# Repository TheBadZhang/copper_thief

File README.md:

# Copper Thief / KiCad 盗铜生成器

在 `Edge.Cuts` 板框内，按规则阵列自动生成**圆形**或**圆角正方形**盗铜（copper thieving），并自动避让已有铜箔、板边、板框开槽、禁布区和钻孔。

> 上图由本插件在 `demo/copper_thief_demo.kicad_pcb` 上实际生成，并经过 KiCad 10.0.6 DRC 验证（0 violations / 0 unconnected）。

---

## 1. 功能

- 图案：圆形，或四边相等的圆角正方形。
- 可调直径 / 边长、圆角半径、阵列净间距。
- 可调铜箔间距、板边间距；实际值会与板级 DRC 规则取较大者。
- 在板框内自动居中，也可设置 X/Y 偏移。
- 支持任意铜层：F.Cu、B.Cu、内层。
- 自动避让：
  - 走线、圆弧走线、过孔、焊盘（含 PTH/NPTH/SMD/自定义焊盘）
  - 已填充的铜区（Zone），包括铜区中的孔洞
  - 铜层上的图形、文字、封装图形
  - 板框开槽、圆孔、异形孔
  - 焊盘/过孔钻孔（含槽孔）
  - 禁布区 / Rule Area（保守处理：整个区域都避开）
- 与已有铜箔相交、间距不足或落在板外时**自动跳过**，并在预览中统计跳过原因。
- 生成结果统一放在一个 `CopperThief` 组中，可用“删除现有盗铜”一键清理。
- 支持“同时避开相同网络铜箔”选项。
- 支持**项目配置文件** `<板名>.copper_thief.json`，可保存任意多个命名配置，下次打开项目直接选择复用。
- 再次生成时可选择“替换整个组”或“追加到同一个组”，不会产生多个难以管理的组。

---

## 2. 安装

### 方式 A：运行安装脚本（推荐）

在 PowerShell 中：

```powershell
cd C:\Users\lab\Desktop\copper_thief
powershell -ExecutionPolicy Bypass -File .\install.ps1
```

默认安装到：

```text
%APPDATA%\kicad\10.0\scripting\plugins\copper_thief
```

如果使用 KiCad 9，可指定版本：

```powershell
powershell -ExecutionPolicy Bypass -File .\install.ps1 -Version 9.0
```

### 方式 B：手动复制

把整个 `copper_thief` 文件夹复制到：

```text
C:\Users\<用户名>\AppData\Roaming\kicad\10.0\scripting\plugins\copper_thief
```

目录结构应为：

```text
...\scripting\plugins\copper_thief\
    __init__.py
    plugin.py
    dialog.py
    core.py
    board_adapter.py
    settings.py
    icon.png
```

然后**完全关闭并重新启动 KiCad PCB Editor**。

### 打开插件

PCB Editor 菜单：

```text
工具 / Tools -> 外部插件 / External Plugins -> Copper Thief (盗铜)
```

插件也会出现在工具栏（铜色圆点图标）。

---

## 3. 快速测试步骤

建议先复制一份 PCB 文件再测试，或先打开自带的 demo：

```text
demo\copper_thief_demo.kicad_pcb
```

### 3.1 在自带 demo 上测试

1. 用 KiCad PCB Editor 打开 `demo\copper_thief_demo.kicad_pcb`。
2. 打开 `工具 -> 外部插件 -> Copper Thief (盗铜)`。
3. 铜层勾选 `F.Cu`。
4. 网络选择 `<无网络>`（第一次测试建议这样，DRC 最干净）。
5. 图案选择“圆角正方形”。
6. 参数建议：
   - 尺寸：`1.2 mm`
   - 圆角半径：`0.25 mm`
   - 阵列间隙：`0.35 mm`
   - 铜箔间距：`0.20 mm`
   - 板边间距：`0.50 mm`
7. 点击“预览数量”，应看到约 1000 个可放置位置。
8. 点击“生成盗铜”。
9. 在 PCB 中查看 `CopperThief` 组；按 `E` 可查看任意一个图形的属性。
10. 打开 `检查 -> 设计规则检查器`，运行 DRC。demo 上应没有新增的间距/短路错误。

### 3.2 在自己的板子上测试

1. 先保存并备份 PCB。
2. 打开插件。
3. 先选择**一个铜层**（例如 `F.Cu`）和 `<无网络>`。
4. 用较小尺寸和较大间隙试跑：
   - 尺寸 `1.0 mm`
   - 间隙 `0.4 mm`
   - 铜箔间距 `0.2 mm`
   - 板边间距 `0.5 mm`
5. 点击“预览数量”，确认数量和跳过统计合理。
6. 点击“生成盗铜”。
7. 查看效果；如果不满意，点击“删除现有盗铜”后重新调整参数。
8. 最后再决定是否给盗铜指定网络。

---

## 4. 参数说明

| 参数 | 说明 |
|---|---|
| 铜层 | 可多选。每个铜层独立计算避让。 |
| 网络 | `<无网络>` 表示不分配网络；选择具体网络后图形会带上该网络。 |
| 形状 | 圆形 / 圆角正方形。圆角正方形四边相等，没有长方形。 |
| 尺寸 | 圆形为直径，正方形为边长。 |
| 圆角半径 | 仅正方形有效，范围 `0 .. 边长/2`。`0` 为直角，`边长/2` 近似圆。 |
| 阵列间隙 | 相邻图形**边缘到边缘**的净间距。中心距 = 尺寸 + 间隙。 |
| 铜箔间距 | 与其它网络铜箔的最小间距。会与板级最小间距、网络类规则、焊盘/铜区局部间距取较大值。 |
| 板边间距 | 与 `Edge.Cuts` 的最小间距。会与板级“铜到板边”规则取较大值。 |
| 自动居中 | 阵列在板框包围盒内居中。 |
| X/Y 偏移 | 在居中（或非居中）基础上平移整个阵列。 |
| 避开相同网络 | 勾选后，已有同网络铜箔也会被避开；取消后只避让不同网络。 |
| 最大尝试数 | 防止参数过小导致几十万次计算。超过会提示调整参数。 |

### 4.1 项目配置与多套参数

插件会在 **PCB 文件同目录**创建：

```text
<板名>.copper_thief.json
```

例如：

```text
uDap.copper_thief.json
```

使用方式：

1. 调整好一套参数；
2. 在“项目配置”下拉框中输入名称，例如“密集”“稀疏”“只 B.Cu”；
3. 点击“保存配置”；
4. 以后打开同一个 PCB，插件会自动读取该文件，选中名称即可载入全部参数；
5. 点“删除”可移除当前选中的配置。

配置文件同时保存：铜层、网络、形状、尺寸、圆角、间隙、间距、偏移、最大尝试数等。

注意：

- 如果 PCB 还没保存到磁盘，无法确定项目目录，此时“保存配置”会提示先保存 PCB。
- 预览或生成盗铜时，当前配置也会自动写入项目配置文件。
- 项目配置和全局设置是两层：项目配置优先；没有项目配置时使用上一次的全局参数。

### 4.2 生成组

所有生成的铜图形会放入同一个 `CopperThief` 组：

- 勾选“生成前删除上一次生成的盗铜”：先删除旧组，再创建一个新组；
- 取消勾选：新图形追加到已有的同一个 `CopperThief` 组，不会产生第二个组。

这样在 KiCad 的组列表中可以一次性选中、隐藏或删除整组盗铜。

---

## 5. 规则与避让说明

插件在生成前会读取：

- 板框 `Edge.Cuts`（含开槽/挖孔）
- 板级设计规则：
  - 最小铜箔间距
  - 铜到板边间距
  - 铜到钻孔间距
- 网络类（Netclass）间距
- 焊盘/铜区/走线的局部间距覆盖（Local Clearance）
- 所有选中铜层上的铜箔：
  - 走线、圆弧走线、过孔
  - 焊盘、通孔、NPTH
  - Zone 的已填充铜皮
  - 铜层上的图形、文字、封装图形
- 禁布区 / Rule Area（保守地整个避开）
- 钻孔和槽孔

任何一个候选位置不满足上述条件都会被跳过，并计入“跳过原因”统计。

### 重要：自定义 DRC 规则

KiCad 的 `.kicad_dru` 自定义规则（例如按区域、按网络名、按封装设置特殊间距）**不会**被插件解析。插件只使用板级设置、网络类和局部间距。生成后仍建议运行一次 DRC。

---

## 6. 关于“指定网络”和 DRC 未连接提示

盗铜通常是**孤立的铜岛**。

- 选择 `<无网络>`：
  - 不会产生网络未连接提示，DRC 最干净。
  - 适合作为纯铜平衡/蚀刻均匀性用途。
- 选择具体网络（例如 `GND`）：
  - 生成的每个图形都会带上该网络。
  - 因为孤岛之间没有走线连接，KiCad DRC 会出现 `unconnected items`（未连接项目）提示。
  - 这是孤立盗铜的电气特性，不是间距/短路错误。
  - 如果必须连接到 GND，请在版图后期用走线、过孔或铜皮把它们连到 GND；或者接受/排除这些未连接提示。
  - 也可以取消“同时避开相同网络的铜箔”，让盗铜有机会与已有同网络铜皮重叠/合并；但是否真正连通仍取决于版图几何。

插件界面和生成后的提示中也会说明这一点。

---

## 7. 找不到可放置位置怎么办

先点 **诊断/导出报告**，插件会生成：

```text
%APPDATA%\kicad\10.0\copper_thief_diagnostic.txt
```

报告会列出板框尺寸、每个铜层的铜箔数量、最大的铜箔/铺铜范围，以及候选位置和跳过原因。把该文件或“结果”框截图发给我即可定位。

也可以点“预览数量”，查看状态栏中的跳过统计：

- **候选位置为 0**：板框内连一个图形都放不下。减小尺寸/圆角/板边间距，并确认 `Edge.Cuts` 没有多余线段。
- **铜箔跳过最多**：所选铜层几乎被已有走线、焊盘或铺铜覆盖。常见原因是该层有一整片 GND 铺铜。
  - 换一个没有整片铺铜的铜层；
  - 如果就是要用 GND 铺铜层，选择 `GND` 网络并取消“同时避开相同网络的铜箔”，让盗铜与铺铜合并（但可能看不出独立铜岛）；
  - 先在铺铜上挖出阵列窗口/禁布区，再生成。
- **禁布跳过最多**：检查 Rule Area / Keepout 是否覆盖了可用区域。
- **板边跳过最多**：检查板框、开槽、挖孔，或减小板边间距。
- **钻孔跳过最多**：可用区域钻孔/安装孔较多，换区域或减小铜箔间距。

未填充或填充数据为空的 Zone 不包含实际铜皮，本插件会忽略它（不会再按轮廓整片避开）。如果希望这些 Zone 参与避让，请先在 KiCad 中重灌铜（`编辑 -> 填充所有铜区`）再试。诊断报告会显示 `unfilled_zones=` 数量。插件日志位于：

```text
%APPDATA%\kicad\10.0\copper_thief.log
```

## 8. 已知限制

- 阵列为**轴对齐规则网格**，暂不支持旋转阵列、交错/蜂窝阵列。
- 只支持圆形和圆角正方形，不支持长方形。
- 未填充/空填充的 Zone 没有实际铜皮，会被忽略；建议先重灌铜再做精确避让。
- Rule Area 无论具体限制类型（禁止过孔/禁止铺铜等）都整体避开（偏保守）。
- 圆弧板框会按 KiCad 多边形离散化，并额外保留 2 µm 规划余量。
- 自定义 `.kicad_dru` 规则不参与计算。
- 生成项是铜层图形（`PCB_SHAPE`），不是焊盘；会放在 `CopperThief` 组中。
- 插件通过 Python API 直接修改当前板，生成前请保存/备份。

---

## 9. 开发与测试

### 9.1 纯逻辑测试（不需要 KiCad）

```powershell
python -m unittest tests.test_core tests.test_settings -v
```

### 9.2 KiCad 集成测试（需要 pcbnew + kicad-cli）

使用 KiCad 自带的 Python（把路径改成你的 KiCad `bin\python.exe`）：

```powershell
$env:COPPER_THIEF_NO_REGISTER = "1"
$env:COPPER_THIEF_SETTINGS = "$PWD\tests\_artifacts\settings.json"
$py = "C:\Program Files\KiCad\10.0\bin\python.exe"
& $py -m unittest tests.test_integration -v
```

测试会：

1. 构造带板框、开槽、走线、焊盘、过孔、Zone、禁布区的板。
2. 生成盗铜。
3. 保存 PCB。
4. 调用 `kicad-cli pcb drc`。
5. 断言没有间距/短路/钻孔相关违规。

### 9.3 重新生成 demo

```powershell
$env:COPPER_THIEF_NO_REGISTER = "1"
$py = "C:\Program Files\KiCad\10.0\bin\python.exe"
& $py demo\make_demo.py
```

---

## 10. 目录结构

```text
copper_thief/
  __init__.py           KiCad 插件注册入口
  plugin.py             ActionPlugin
  dialog.py             wxPython 界面
  core.py               纯 Python 几何、避让、阵列规划
  board_adapter.py      pcbnew 读取/生成适配层
  settings.py           参数持久化
  icon.png              插件图标
  install.ps1           Windows 安装脚本
  .github/workflows/release.yml  v* 标签自动构建并发布 Release
  tests/
    test_core.py        算法单元测试
    test_settings.py    项目配置/多配置读写测试
    test_integration.py pcbnew + DRC 集成测试
  demo/
    make_demo.py        demo 生成脚本
    copper_thief_demo.kicad_pcb
    preview.png
```

运行插件后，PCB 同目录会生成：

```text
<板名>.copper_thief.json
```

---

## 11. 版本记录

- **1.2.0**：新增 PCB 同目录项目配置文件 `<板名>.copper_thief.json`，支持任意多个命名配置的保存、载入和删除；生成项始终归入同一个 `CopperThief` 组，支持替换或追加；新增 `v*` 标签自动构建并发布 GitHub Release 的 workflow。
- **1.1.0**：修复“有 Zone 轮廓但没有实际填充数据”时被误判为整板铜皮、导致 0 个可放置位置的问题；未填充/空填充 Zone 现在会被忽略。新增“诊断/导出报告”按钮。
- **1.0.0**：初始版本。

## 12. 许可

MIT License，见 [LICENSE](LICENSE)。

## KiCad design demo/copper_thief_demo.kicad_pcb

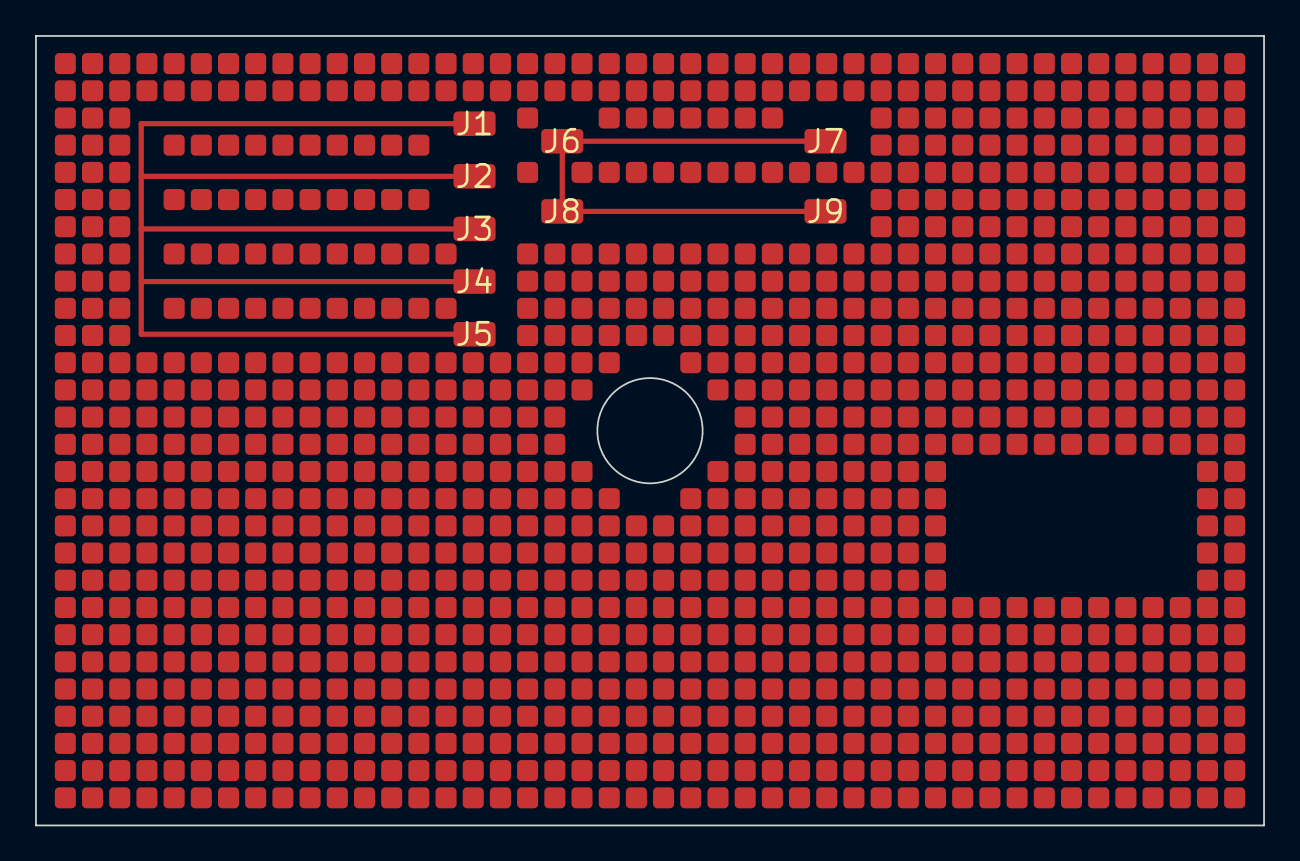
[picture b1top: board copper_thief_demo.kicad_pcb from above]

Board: 2 copper layers, 70.0 x 45.0 mm, 9 parts (0 on the bottom side), 2 nets.

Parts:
J1, J2, J3, J4, J5, J6, J7, J8, J9: DEMO

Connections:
GND: J1.1, J2.1, J3.1, J4.1, J5.1
SIG: J6.1, J7.1, J8.1, J9.1

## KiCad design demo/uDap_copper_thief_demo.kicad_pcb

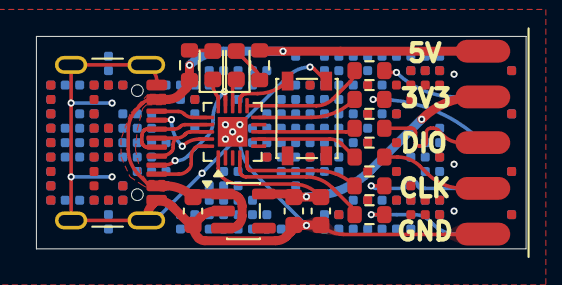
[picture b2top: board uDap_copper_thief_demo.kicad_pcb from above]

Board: 2 copper layers, 27.2 x 11.8 mm, 18 parts (0 on the bottom side), 26 nets.

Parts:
C1, C2: 1uF; C_0603_1608Metric
C3: 0.1uF; C_0603_1608Metric
D1, D2: LED; LED_0603_1608Metric
J1: USB_C_Receptacle_USB2.0_16P; USB_C_Receptacle_GCT_USB4105-xx-A_16P_TopMnt_Horizontal
J3: Conn_02x05_Odd_Even; 双面贴片排针2x5
R1, R2, R3, R4, R5, R6: 47R; R_0603_1608Metric
R7, R9: 4.7K; R_0603_1608Metric
SW3: SW_MEC_5E; KEY-SMD_4P-L4.2-W3.4-P2.15-LS4.5-TL_1
U1: CH32X035F8U6; QFN-20-1EP_3x3mm_P0.4mm_EP1.65x1.65mm
U2: RT9013; SOT-23-5

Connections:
+3V3: C2.1, C3.1, J3.3, U1.1 (VDD), U2.5 (VOUT)
+5V: C1.1, J1.A4 (VBUS), J1.A9 (VBUS), J1.B4 (VBUS), J1.B9 (VBUS), J3.1, R7.1, R9.1, U2.1 (VIN), U2.3 (EN)
/CC1: J1.A5 (CC1), U1.19 (CC1)
/CC2: J1.B5 (CC2), U1.20 (CC2)
/CLK: R4.1, U1.7 (PA5)
/CLK_: J3.7, R4.2
/D+: J1.A6 (D+), J1.B6 (D+), U1.18 (UDP)
/D-: J1.A7 (D-), J1.B7 (D-), U1.17 (UDM)
/DIO: R3.1, U1.8 (PA6)
/DIO_: J3.5, R3.2
/LED_DAP: D1.1 (K), U1.13 (PB11)
/LED_UART: D2.1 (K), U1.15 (PB12)
/RVDCK: J1.B8 (SBU2), U1.16 (DCK)
/RVDIO: J1.A8 (SBU1), U1.14 (DIO)
/RX: R1.1, U1.11 (RX4)
/RX2: R5.1, U1.5 (RX2)
/RX2_: J3.8, R5.2
/RX_: J3.4, R1.2
/TX: R2.1, U1.10 (TX4)
/TX2: R6.1, U1.4 (TX2)
/TX2_: J3.10, R6.2
/TX_: J3.6, R2.2
GND: C1.2, C2.2, C3.2, J1.A1 (GND), J1.A12 (GND), J1.B1 (GND), J1.B12 (GND), J1.SH (SHIELD), J3.9, SW3.4 (A), U1.21 (GND), U2.2 (GND)
unnamed: D1.2 (A), R7.2
unnamed: D2.2 (A), R9.2
unnamed: SW3.2, U1.12 (PB3)
